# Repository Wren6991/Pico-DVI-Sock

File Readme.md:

Pico DVI Sock
=============

You surface mount solder the Raspberry end of your Pico on top of this board (thanks to the castellations on Pico's header footprints). This gives you an HDMI-shaped socket at the opposite end to the micro USB socket, which you can drive DVI-D video through. The remaining Pico pins can still have headers inserted, so that the board can be inserted into a breadboard.

[See the schematic (PDF)](dvi-sock.pdf)

The PCB layout is compatible with JLCPCB 2-layer prototyping service. Select **1mm** board thickness when you check out (no extra cost).

> :warning: **This board was created with KiCad Nightly (5.99).** Exported gerbers are in `gerb/`, so you can order PCBs without installing this version of KiCad.

Bill of Materials
-----------------

- 1× Stewart SS-53000-001 connector [(DigiKey link)](https://www.digikey.co.uk/product-detail/en/stewart-connector/SS-53000-001/380-SS-53000-001-ND/10492172)
- 8× 0402 270 ohm resistors
- _(optional)_ 1× 2-pin 2.54 mm header to supply +5V to the Sink

Soldering Tips (Fitting Sock to Pico)
-------------------------------------

The Raspberry end of Pico should be surface-mount soldered on top of the Sock. The image below shows the correct orientation: the last 5 castellated holes on each long edge of Pico align with 5 pads on the Sock, to connect GP12-19 and GND on Pico to the TMDS pairs and signal ground. The text saying "Surface-mount Pico Here" on top of the Sock should be covered by the Pico.

Aligned in this way, there is surface-to-surface contact between each metal pad on the Sock, and the corresponding metal pad on Pico. To successfully solder the two boards, we need to flow solder into the narrow gap between the two pads, in a thin film that *wets* both surfaces to create a strong mechanical and electrical bond. The trick here is to get both pads hot simultaneously, melt solder onto one of the pads, and let surface tension do the work.

> :information_source: **To help get the two boards aligned**, you might find it helpful to push a 3-pin header through the debug contacts (without soldering it yet), as shown in the next image.

Things to note in the above image:

- The soldering iron is in contact with the flat upper surface of the surface mount pad on the Sock, and *simultaneously* touches the castellation surface on the side of Pico, so that both pads are brought up to soldering temperatures simultaneously.
- The solder is fed onto the castellated surface, and melted by the heat of the pad, **not** directly by the iron.
    - This is generally true in soldering: you heat the two surfaces you want to solder, and then melt solder onto those surfaces
    - This lets the flux in the solder work its magic, and clean the surfaces of oxidation as you solder, so that you get a strong joint
    - It also ensures the surface you are soldering is at a temperature where it can be *wetted* by the solder, i.e. surface tension will spread solder across the surface in a film, instead of sitting on top in a useless blob

> :warning: **I recommend just soldering the 5 pads along each edge,** and not the 3 debug pads at this point. It's too easy to get a solder blob on the surface-mount resistors when trying to solder the debug pads.

Pico and the Sock are both thinner than usual PCBs (1mm each) so the debug pin header can be pushed through both boards, and through-hole soldered from the back as normal:

- Bring the soldering iron in contact with the pad surface and the side of the header pin, so that both get hot simultaneously
- Introduce solder from the opposite side to the iron, so that surface tension sucks the solder into the hole and creates a strong joint
- You might want to keep the iron there for a little longer so that solder can flow down onto the Pico's through-hole pad, as well as the one on the Sock

Once the Sock is mounted, you can populate the remaining through-holes on Pico with 2.54 mm headers if you choose, so the board can be pushed into a breadboard.

Finally, an alternative if you want to avoid surface mount soldering: you can push headers into Pico from the bottom, sit the Sock onto the stubs of the headers that are sticking through, and then through-hole solder from the top, like shown here:

> :warning: **You should cut off the last 5 pins on each side** (GP12-GP19 and the two GNDs, which connect through the Sock), if you solder the boards this way and intend to plug this board into a breadboard, so that the high-speed serial video signals aren't connected to the breadboard parasitics.

Soldering Tips (Assembling a DVI Sock)
--------------------------------------

- Use flux
- Fine-pitch surface mount components can smell fear. Show them who's boss
- Get multiple spare sets of components and PCBs
- **Use lots of flux**
- These PCBs are pretty tiny so you want something to hold them. I recommend a Stickvise (or knock off), like shown here:

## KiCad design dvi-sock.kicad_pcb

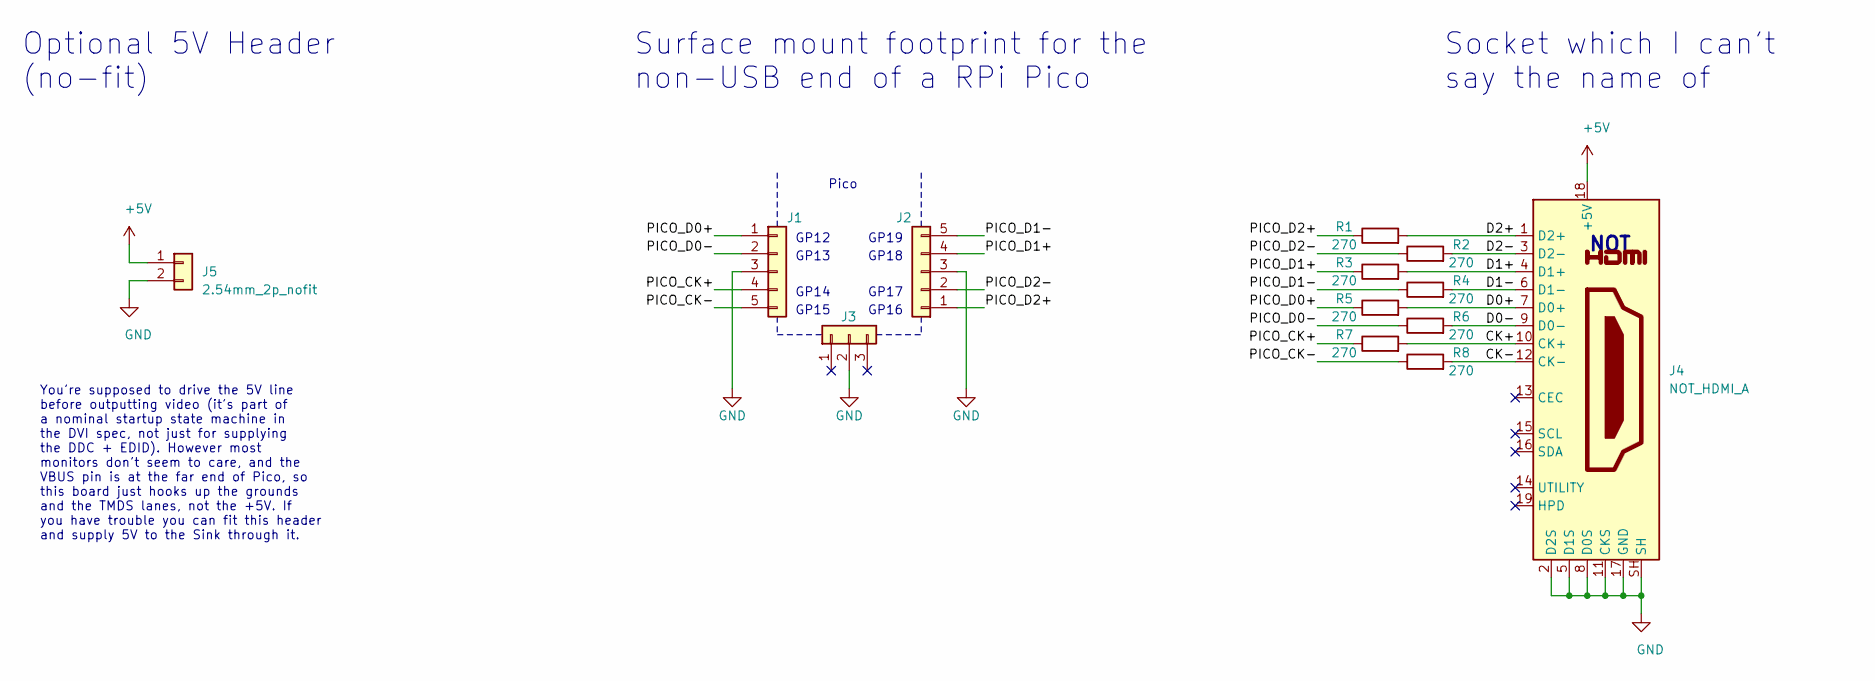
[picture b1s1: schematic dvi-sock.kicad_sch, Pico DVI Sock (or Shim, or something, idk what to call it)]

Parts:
J1, J2: Conn_01x05; castellated_2.54mm_smd_x5
J3: Conn_01x03; castellated_2.54mm_smd_x3
J4: NOT_HDMI_A; HDMI-SS-53000
J5: 2.54mm_2p_nofit; PinHeader_1x02_P2.54mm_Vertical_nosilk
R1, R2, R3, R4, R5, R6, R7, R8: 270; R_0402_1005Metric

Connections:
+5V: J4.18 (+5V), J5.1
/CK+: J4.10 (CK+), R7.2
/CK-: J4.12 (CK-), R8.2
/D0+: J4.7 (D0+), R5.2
/D0-: J4.9 (D0-), R6.2
/D1+: J4.4 (D1+), R3.2
/D1-: J4.6 (D1-), R4.2
/D2+: J4.1 (D2+), R1.2
/D2-: J4.3 (D2-), R2.2
/PICO_CK+: J1.4, R7.1
/PICO_CK-: J1.5, R8.1
/PICO_D0+: J1.1, R5.1
/PICO_D0-: J1.2, R6.1
/PICO_D1+: J2.4, R3.1
/PICO_D1-: J2.5, R4.1
/PICO_D2+: J2.1, R1.1
/PICO_D2-: J2.2, R2.1
GND: J1.3, J2.3, J3.2, J4.2 (D2S), J4.5 (D1S), J4.8 (D0S), J4.11 (CKS), J4.17 (GND), J4.SH, J5.2

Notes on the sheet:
Optional 5V Header (no-fit)
You're supposed to drive the 5V line before outputting video (it's part of a nominal startup state machine in the DVI spec, not just for supplying the DDC + EDID). However most monitors don't seem to care, and the VBUS pin is at the far end of Pico, so this board just hooks up the grounds and the T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
Surface mount footprint for the non-USB end of a RPi Pico
GP12
GP13
GP14
GP15
Pico
GP19
GP18
GP17
GP16
Socket which I can't say the name of
NOT

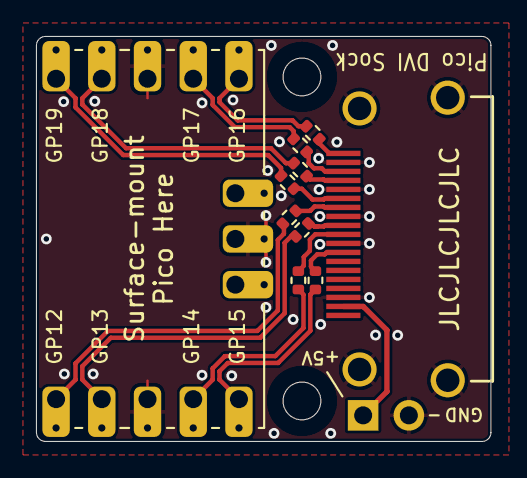
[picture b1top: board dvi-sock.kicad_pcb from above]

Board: 2 copper layers, 25.2 x 22.5 mm, 13 parts (0 on the bottom side), 18 nets.

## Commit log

2021-02-01 Schematic, initial component placement
2021-02-02 Routed, DRC clean
2021-02-02 Rounded corners, license, readme
2021-02-02 Oops, missing via
2021-02-02 add bom to readme
2021-02-02 Tweak clock lane grounding, add optional 5V header
2021-02-02 Tweak silkscreen layout/orientation to match Pico
2021-02-02 Small silkscreen tweak, enlarge header holes to 1mm from 0.9mm
2021-02-02 Export gerbers
2021-02-02 Update name/date on schematic
2021-02-22 Add soldering tips to readme
